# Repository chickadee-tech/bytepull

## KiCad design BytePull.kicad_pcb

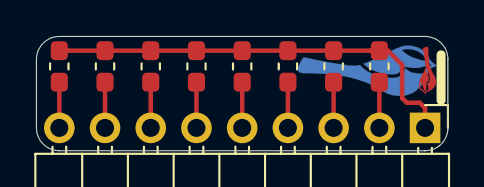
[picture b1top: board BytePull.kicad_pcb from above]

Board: 2 copper layers, 22.9 x 6.4 mm, 9 parts (0 on the bottom side), 9 nets.

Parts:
J1: Conn_01x09_Male; PinHeader_1x09_P2.54mm_Horizontal
R1, R2, R3, R4, R5, R6, R7, R8: 10k; R_0603_1608Metric_Pad1.05x0.95mm_HandSolder

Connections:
unnamed: J1.1, R1.1, R2.1, R3.1, R4.1, R5.1, R6.1, R7.1, R8.1
unnamed: J1.2, R1.2
unnamed: J1.3, R2.2
unnamed: J1.4, R3.2
unnamed: J1.5, R4.2
unnamed: J1.6, R5.2
unnamed: J1.7, R6.2
unnamed: J1.8, R7.2
unnamed: J1.9, R8.2
